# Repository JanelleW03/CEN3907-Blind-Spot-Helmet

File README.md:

# CEN4908-Blind-Spot-Helmet
Urban cyclists face safety risks from traffic and limited visibility. Traditional helmets protect the head but don’t enhance awareness. The Blind Spot Helmet uses radar-based detection and haptic feedback to alert riders of nearby vehicles in real time, improving safety for daily commuters on busy streets.

At a high level, our current architecture for this project is as follows. We utilize a Raspberry Pi 4 to poll two LiDAR sensors and interpret if there are any objects present within a predetermined range that could pose a risk to the user. If the LiDARs identify a potentially dangerous object, a haptic feedback sensor will be activated on the side that the object was detected to alert the user of its presence.

# Completed Work
We developed fully functioning code for the Pi 4 that polls the LiDAR sensors and successfully triggers haptic feedback on the side where an object was detected. 

In parallel, we are working on an implementation for the Raspberry Pi Pico, which is much more portable and consumes less power. At this point, we are currently testing LiDAR integration with Pico-specific code.

As for physical components within the project, we have gone through many iterations of 3d modules to house our system. The current one is robust and houses the Raspberry Pi as well as the sensors connected to it, with cutouts for charging and wiring.

# Known Bugs
The only main bug we have for our design at the moment is due to the physical connections between Raspberry Pi and sensors. Because we haven't soldered connections, as we are still testing multiple systems, our wiring is liable to disconnections during movement testing. This will be fixed once we have finalized our design and implement permanent connections.

# Onshape Design of Helmet Module
Copy and past this link into your browser to view:
https://cad.onshape.com/documents/718453d0fac994bf19ba09c7/w/0e19fb7305c1e5489b3984cd/e/3690a92add8a8350898fd115?renderMode=0&uiState=69992da93609fa864f87f9de

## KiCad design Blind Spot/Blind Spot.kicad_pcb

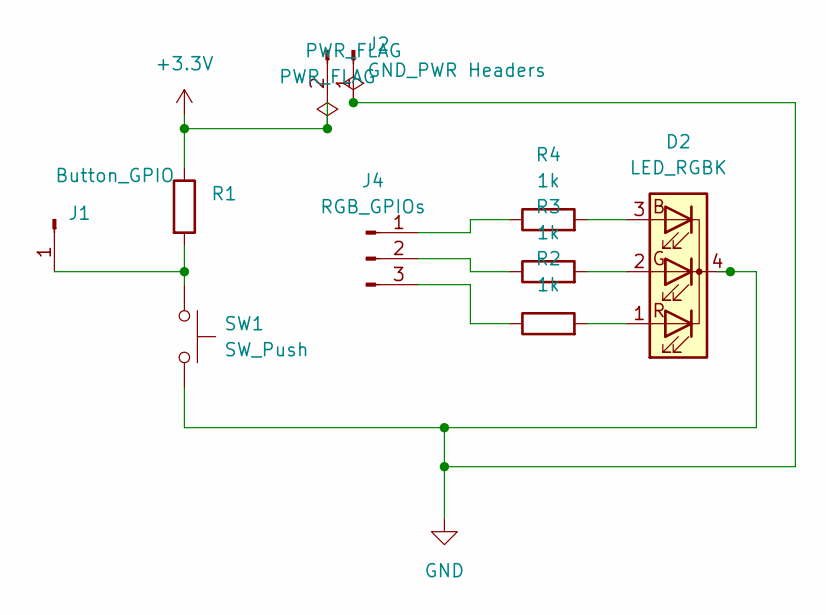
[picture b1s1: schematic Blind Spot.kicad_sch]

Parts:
D2: LED_RGBK; LED_D5.0mm-4_RGB
J1: Button_GPIO; PinHeader_1x03_P2.54mm_Vertical
J2: GND_PWR Headers; PinHeader_1x02_P2.54mm_Vertical
J4: RGB_GPIOs; PinHeader_1x03_P2.54mm_Vertical
R1, R2, R3, R4: 1k; R_0805_2012Metric
SW1: SW_Push; SW_PUSH_6mm

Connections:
+3.3V: J2.2, R1.1
GND: D2.4 (K), J2.1, SW1.2
unnamed: D2.3 (BA), R4.2
unnamed: D2.2 (GA), R3.2
unnamed: D2.1 (RA), R2.2
unnamed: J1.1, R1.2, SW1.1
unnamed: J4.1, R4.1
unnamed: J4.2, R3.1
unnamed: J4.3, R2.1

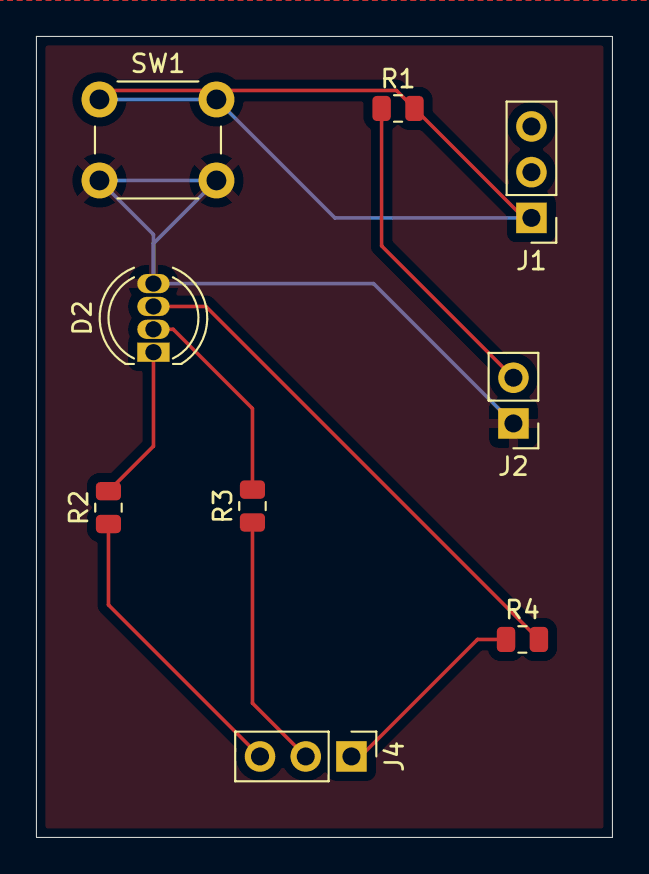
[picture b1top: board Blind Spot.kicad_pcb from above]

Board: 2 copper layers, 32.0 x 44.5 mm, 9 parts (0 on the bottom side), 9 nets.

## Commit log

2025-10-23 Add Pre-Alpha build code for ultrasonic distance sensor
    Code for tinkercad pre-alpha build prototype. The parts used here will not be used in the future and we will most likely use a raspberry pi. This is purely meant to demonstrates the core of our proje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
2025-10-25 Add files via upload
    Outline of how vehicle versus pedestrian detection will work
2025-10-25 Add files via upload
    Simple rough draft of a possible CNN
2025-10-27 Uploaded initial mockup drawing of helmet design
2025-11-07 Add files via upload
    radar test code
2025-11-07 arduino code changes
2025-11-07 faster radar sensor
2025-11-10 Add files via upload
    Trained model on Kaggle dataset, high accuracy
2025-11-13 RX and TX confusion fixed
2025-11-13 demo code
2025-11-15 Helmet Module Prototype made on Onshape
    https://cad.onshape.com/documents/718453d0fac994bf19ba09c7/w/0e19fb7305c1e5489b3984cd/e/772e344e4bcf35f5efbb1f72?renderMode=0&uiState=6918dec4ba028ae2e74cdf1d
2025-11-16 Create script to setup camera
2025-11-16 code for demo
2025-11-17 add utils.py
2025-11-17 add detect.py
2025-11-18 Add setup script for ML camera model
2026-01-15 time log setup
2026-01-15 time log
2026-01-19 log update
2026-01-20 Update Time Log Notes
2026-01-20 raspberry pi sensor and haptic test
2026-01-20 time log from sem 1 & new logs
2026-01-20 housekeeping
2026-01-20 1/20 update
2026-01-20 test updated
2026-01-20 additions to fully functional test code
2026-01-21 added Gabriel Design I time log
2026-01-21 added entries to Gabriel_timelog
2026-01-21 Add meeting notes to time log
2026-01-22 time log + tensorflow model
2026-01-22 Drew sketches of potential product for alpha build
2026-01-22 1/22 updatae
2026-01-22 update time log
2026-01-22 LiDar test & UART functionality
2026-01-23 alpha build test
2026-01-26 Add meeting notes for 3D model housing discussion
2026-01-26 Update Ana - Time Log Notes
2026-01-26 test alpha build semester 2
2026-01-26 fixed alpha with no known bugs
2026-01-27 changing obj detection model to run without visualization and basic gpio setup
2026-01-27 time log notes
2026-01-27 reorg files
2026-01-29 lidar with headless camera detection
2026-01-29 time log update
2026-01-30 Update README.md with link to Onshape
2026-02-02 code with button UI
2026-02-02 finish UD and lidar code for demo
2026-02-03 button code
2026-02-03 button
2026-02-10 update camera and haptic code
2026-02-10 systemd service file for running program on startup
2026-02-10 fix service file
2026-02-11 Update time log with recent activities
    Added new entries for meetings and work sessions.
2026-02-11 Update time log entries with correct dates
2026-02-12 LED UI and UD removed
2026-02-12 RGB LED edits
2026-02-12 update 2/12
2026-02-17 Update time log with recent activities
    Added notes for systemd script initiation and beta check-in meeting.
2026-02-17 Update alphaBuild.py
    Updated based on working Raspberry Pi code
2026-02-17 Update alphaBuild.py
    Changed some GPIO pin assignments for ease of access on physical module
2026-02-17 code for two lidars, and changed original alphaBuild.py to check for longer distances
2026-02-17 PCB files
    The main pcb files to be reviewed are the blind spot.kicad_sch and the blind spot.kicad_pcb. all of the other files are the production files that come from building the gerber plot
2026-02-17 Add entries for PCB work on 2/13 and 2/17
2026-02-17 Revise PCB entry for 2/13 with design changes
    Updated time log entry for 2/13 to include design changes for GPIO ports.
2026-02-17 Update time log with recent meeting notes and tasks
    Added new entries for meetings and progress updates on PCB work.
2026-02-19 Zipped Gerber files
    This zipped folder has everything we need to send the pcb to get produced
2026-02-19 implement functioning code to test LIDAR with Pico
2026-02-21 Revise time log with detailed meeting and work entries
    Updated time log with detailed entries for meetings and individual work, specifying hours and activities.
2026-02-21 Revise README to update project architecture and progress
    Updated project details to reflect changes in architecture and functionality, including the use of LiDAR sensors and Raspberry Pi integration.
2026-02-21 Update time log with recent testing and integration details
2026-02-21 Update README.md
    Re-added Onshape link
2026-02-21 Update README.md
    Added instructions for Onshape link
2026-02-22 working LED
2026-02-22 LED edits
2026-02-22 typo fix
2026-02-23 Time log updates
2026-03-02 camera with led/lidar/button code:
2026-03-03 Update time log with recent activities and tests
2026-03-05 update 3/4
2026-03-26 Add time log entries for march
2026-04-21 Update time log with additional entries and corrections
2026-04-21 added helmet code
2026-04-21 deleted object-detect
2026-04-22 Change project name in README
    Updated project name in README from CEN3907 to CEN4908.
2026-04-23 Add time log entries for project meetings and testing
2026-04-23 Correct time log entries and update task details
    Updated time log entries with corrected hours and additional details for various tasks.
